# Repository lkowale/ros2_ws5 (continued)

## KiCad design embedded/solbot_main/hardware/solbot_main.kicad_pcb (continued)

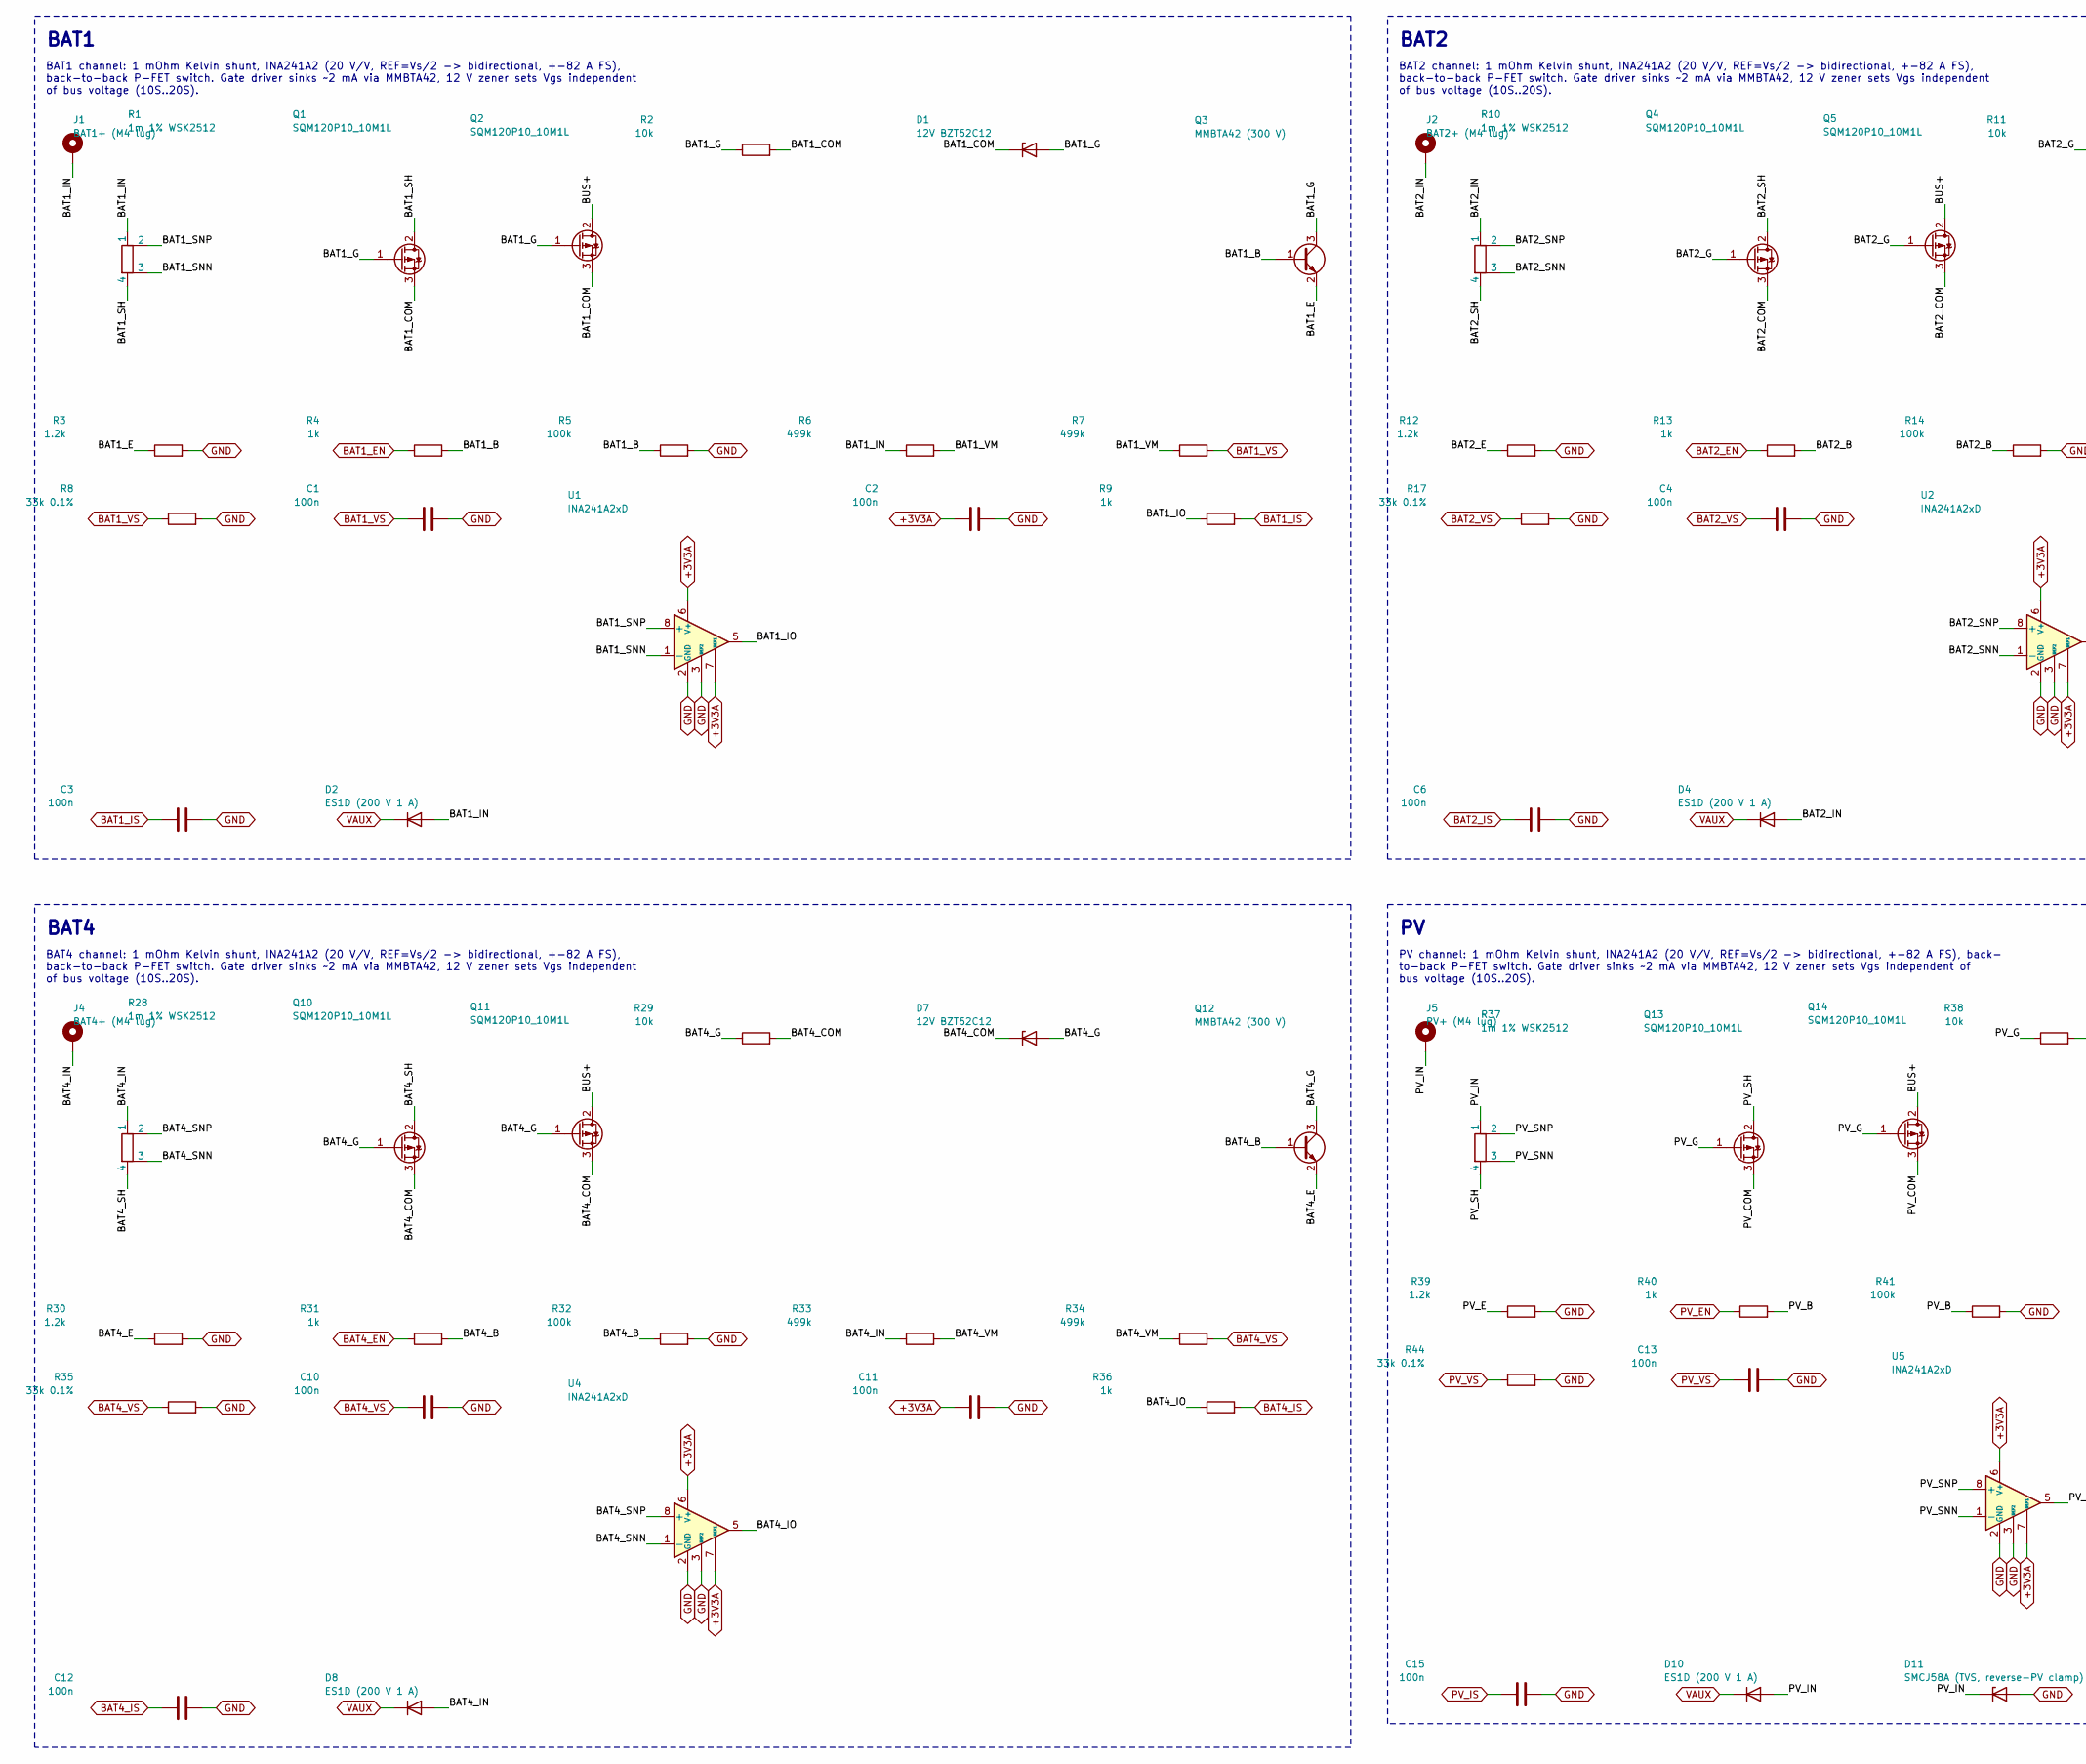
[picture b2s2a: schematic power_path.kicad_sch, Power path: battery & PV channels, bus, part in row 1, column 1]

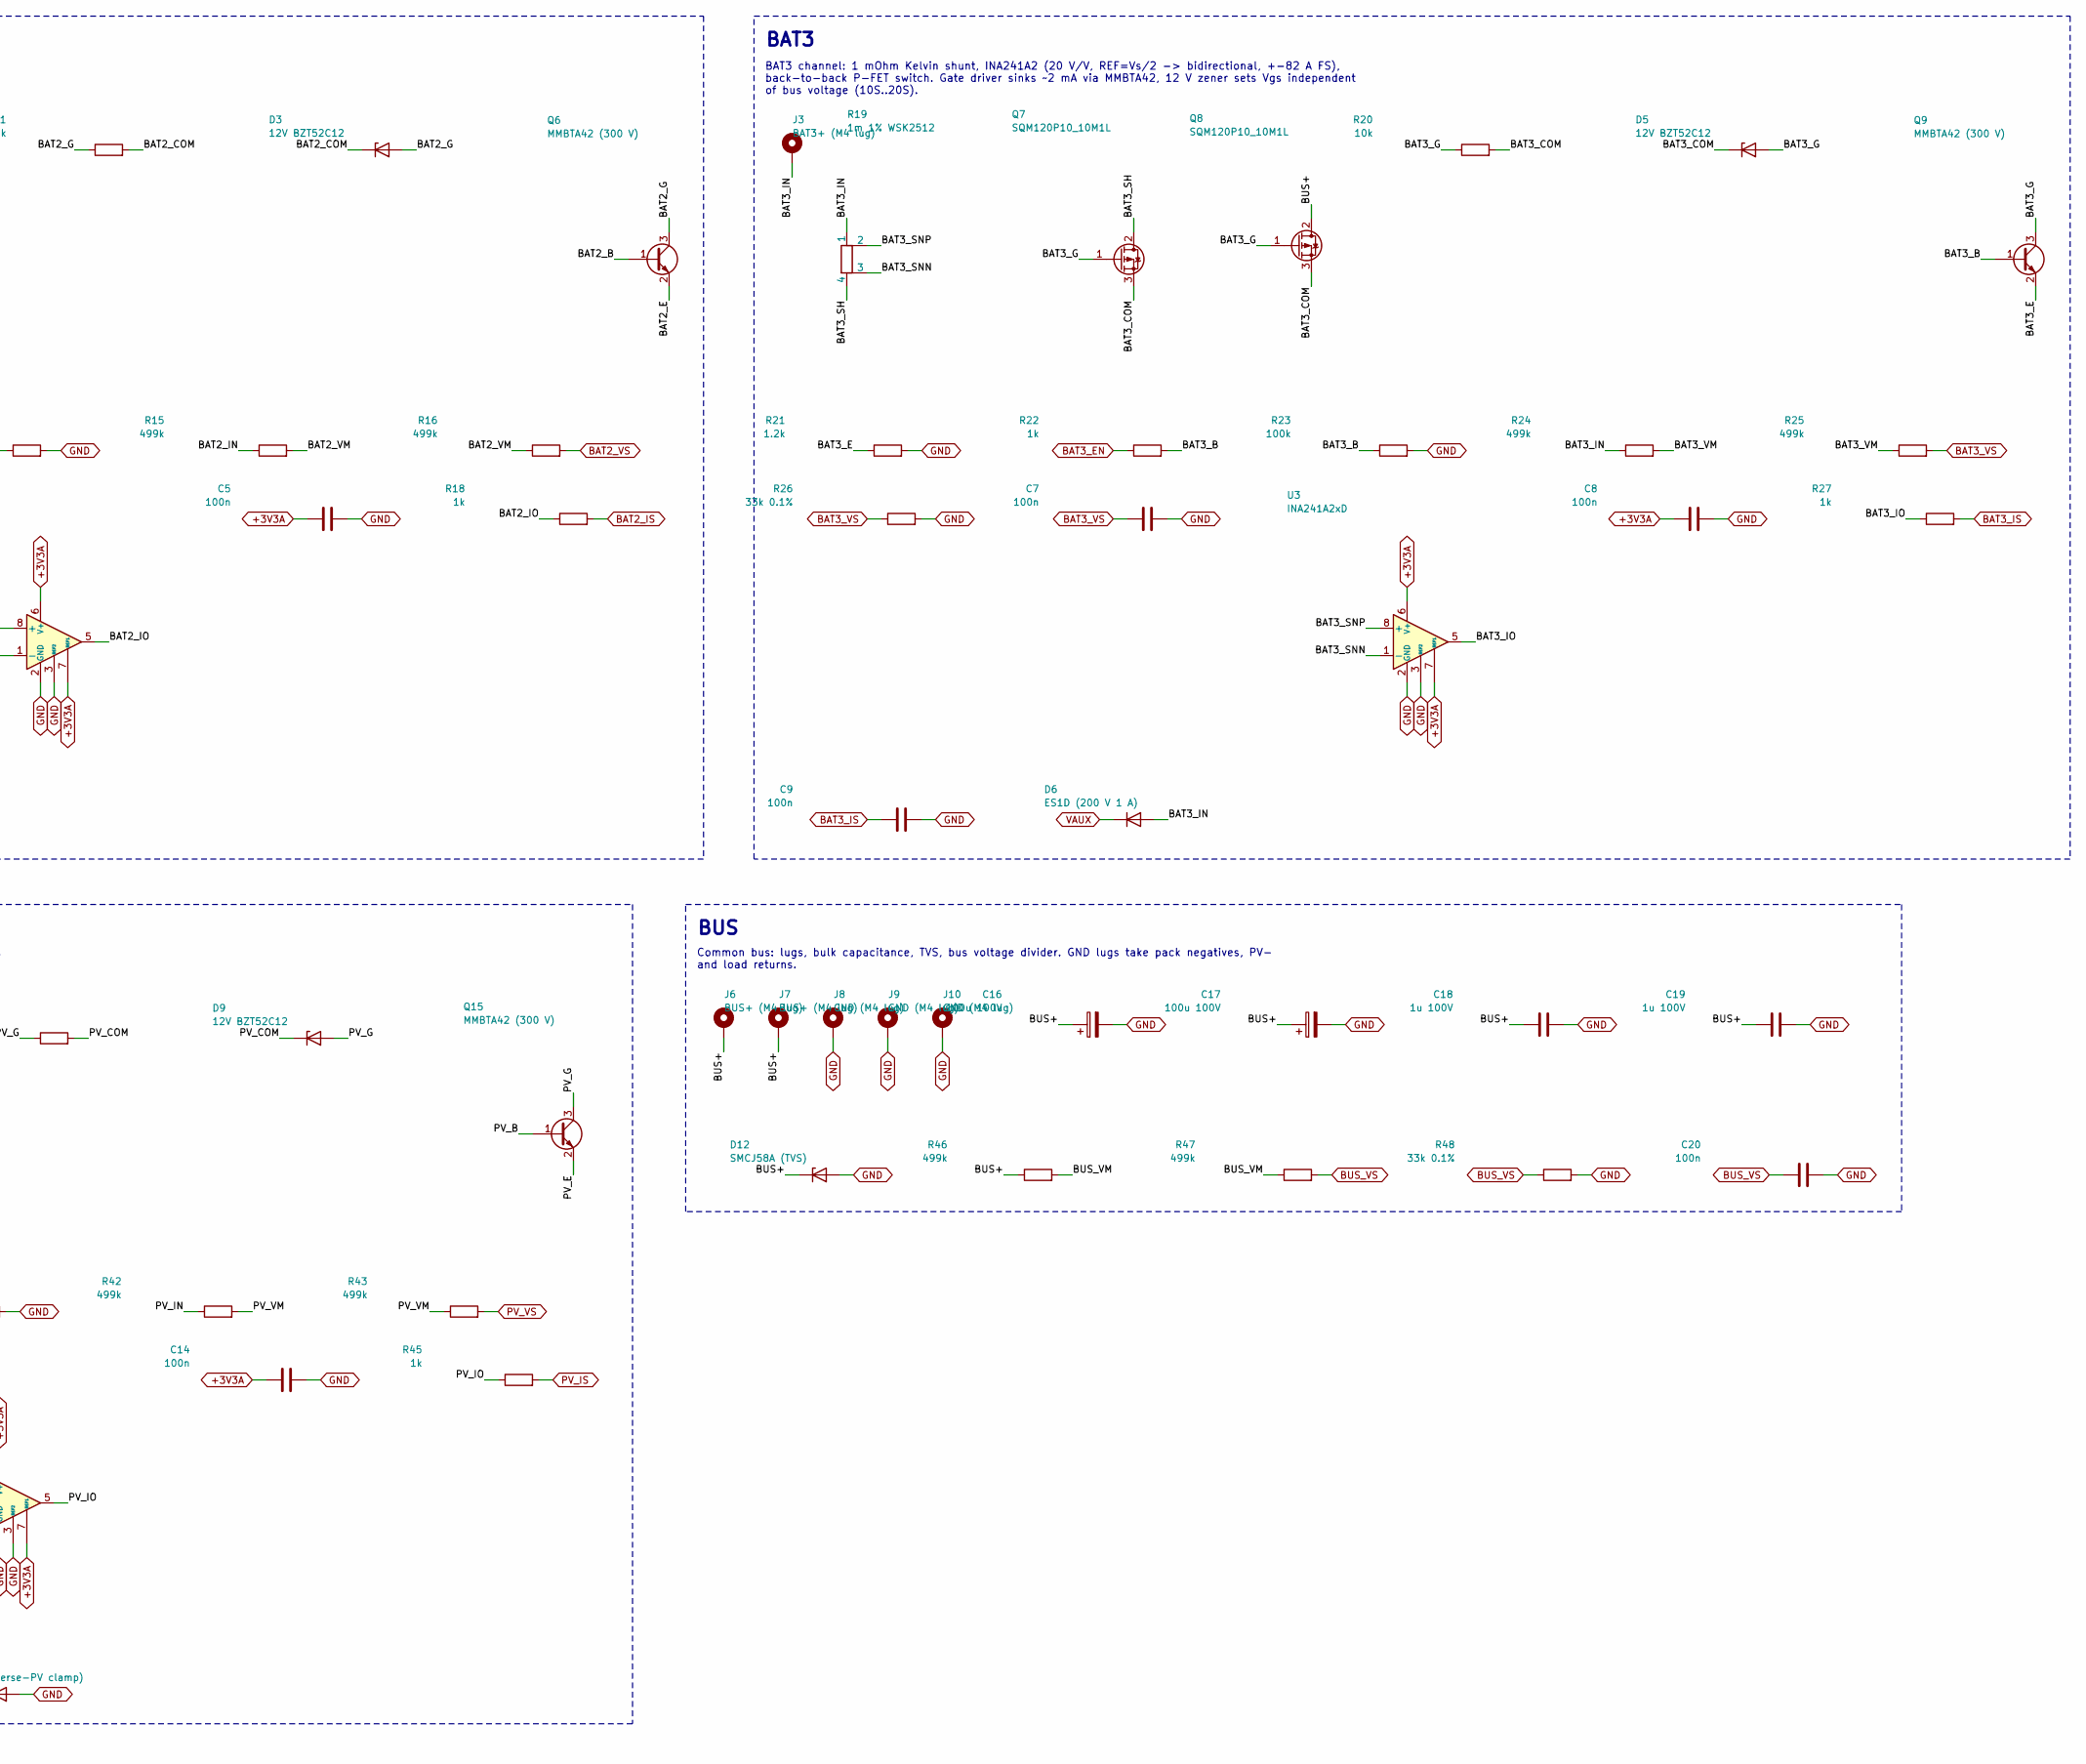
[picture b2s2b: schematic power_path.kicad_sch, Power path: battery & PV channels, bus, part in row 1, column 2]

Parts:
C1, C2, C3, C4, C5, C6, C7, C8, C9, C10, C11, C12, C13, C14, C15, C20: 100n; C_0603_1608Metric
C16, C17: 100u 100V; CP_Radial_D12.5mm_P5.00mm
C18, C19: 1u 100V; C_1210_3225Metric
D1, D3, D5, D7, D9: 12V BZT52C12; D_SOD-123
D2, D4, D6, D8, D10: ES1D (200 V 1 A); D_SMA
D11: SMCJ58A (TVS, reverse-PV clamp); D_SMC
D12: SMCJ58A (TVS); D_SMC
J1: BAT1+ (M4 lug); MountingHole_4.3mm_M4_Pad_Via
J2: BAT2+ (M4 lug); MountingHole_4.3mm_M4_Pad_Via
J3: BAT3+ (M4 lug); MountingHole_4.3mm_M4_Pad_Via
J4: BAT4+ (M4 lug); MountingHole_4.3mm_M4_Pad_Via
J5: PV+ (M4 lug); MountingHole_4.3mm_M4_Pad_Via
J6, J7: BUS+ (M4 lug); MountingHole_4.3mm_M4_Pad_Via
J8, J9, J10: GND (M4 lug); MountingHole_4.3mm_M4_Pad_Via
Q1, Q2, Q4, Q5, Q7, Q8, Q10, Q11, Q13, Q14: SQM120P10_10M1L; TO-263-2; MPN Vishay SQM120P10_10M1L (-100 V, 10 mOhm)
Q3, Q6, Q9, Q12, Q15: MMBTA42 (300 V); SOT-23
R1, R10, R19, R28, R37: 1m 1% WSK2512; R_Shunt_Vishay_WSK2512_6332Metric_T1.19mm; MPN Vishay WSK25121L000FEA
R2, R11, R20, R29, R38: 10k; R_0603_1608Metric
R3, R12, R21, R30, R39: 1.2k; R_0603_1608Metric
R4, R9, R13, R18, R22, R27, R31, R36, R40, R45: 1k; R_0603_1608Metric
R5, R14, R23, R32, R41: 100k; R_0603_1608Metric
R6, R7, R15, R16, R24, R25, R33, R34, R42, R43, R46, R47: 499k; R_1206_3216Metric
R8, R17, R26, R35, R44, R48: 33k 0.1%; R_0603_1608Metric
U1, U2, U3, U4, U5: INA241A2xD; SOIC-8_3.9x4.9mm_P1.27mm

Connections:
+3V3A: C2.1, C5.1, C8.1, C11.1, C14.1, U1.6 (V+), U1.7 (REF1), U2.6 (V+), U2.7 (REF1), U3.6 (V+), U3.7 (REF1), U4.6 (V+), U4.7 (REF1), U5.6 (V+), U5.7 (REF1); also elsewhere on the board
BAT1_B: Q3.1 (B), R4.2, R5.1
BAT1_COM: D1.1 (K), Q1.3 (S), Q2.3 (S), R2.2
BAT1_E: Q3.2 (E), R3.1
BAT1_EN: R4.1; also elsewhere on the board
BAT1_G: D1.2 (A), Q1.1 (G), Q2.1 (G), Q3.3 (C), R2.1
BAT1_IN: D2.2 (A), J1.1, R1.1, R6.1
BAT1_IO: R9.1, U1.5
BAT1_IS: C3.1, R9.2; also elsewhere on the board
BAT1_SH: Q1.2 (D), R1.4
BAT1_SNN: R1.3, U1.1 (-)
BAT1_SNP: R1.2, U1.8 (+)
BAT1_VM: R6.2, R7.1
BAT1_VS: C1.1, R7.2, R8.1; also elsewhere on the board
BAT2_B: Q6.1 (B), R13.2, R14.1
BAT2_COM: D3.1 (K), Q4.3 (S), Q5.3 (S), R11.2
BAT2_E: Q6.2 (E), R12.1
BAT2_EN: R13.1; also elsewhere on the board
BAT2_G: D3.2 (A), Q4.1 (G), Q5.1 (G), Q6.3 (C), R11.1
BAT2_IN: D4.2 (A), J2.1, R10.1, R15.1
BAT2_IO: R18.1, U2.5
BAT2_IS: C6.1, R18.2; also elsewhere on the board
BAT2_SH: Q4.2 (D), R10.4
BAT2_SNN: R10.3, U2.1 (-)
BAT2_SNP: R10.2, U2.8 (+)
BAT2_VM: R15.2, R16.1
BAT2_VS: C4.1, R16.2, R17.1; also elsewhere on the board
BAT3_B: Q9.1 (B), R22.2, R23.1
BAT3_COM: D5.1 (K), Q7.3 (S), Q8.3 (S), R20.2
BAT3_E: Q9.2 (E), R21.1
BAT3_EN: R22.1; also elsewhere on the board
BAT3_G: D5.2 (A), Q7.1 (G), Q8.1 (G), Q9.3 (C), R20.1
BAT3_IN: D6.2 (A), J3.1, R19.1, R24.1
BAT3_IO: R27.1, U3.5
BAT3_IS: C9.1, R27.2; also elsewhere on the board
BAT3_SH: Q7.2 (D), R19.4
BAT3_SNN: R19.3, U3.1 (-)
BAT3_SNP: R19.2, U3.8 (+)
BAT3_VM: R24.2, R25.1
BAT3_VS: C7.1, R25.2, R26.1; also elsewhere on the board
BAT4_B: Q12.1 (B), R31.2, R32.1
BAT4_COM: D7.1 (K), Q10.3 (S), Q11.3 (S), R29.2
BAT4_E: Q12.2 (E), R30.1
BAT4_EN: R31.1; also elsewhere on the board
BAT4_G: D7.2 (A), Q10.1 (G), Q11.1 (G), Q12.3 (C), R29.1
BAT4_IN: D8.2 (A), J4.1, R28.1, R33.1
BAT4_IO: R36.1, U4.5
BAT4_IS: C12.1, R36.2; also elsewhere on the board
BAT4_SH: Q10.2 (D), R28.4
BAT4_SNN: R28.3, U4.1 (-)
BAT4_SNP: R28.2, U4.8 (+)
BAT4_VM: R33.2, R34.1
BAT4_VS: C10.1, R34.2, R35.1; also elsewhere on the board
BUS+: C16.1, C17.1, C18.1, C19.1, D12.1 (K), J6.1, J7.1, Q2.2 (D), Q5.2 (D), Q8.2 (D), Q11.2 (D), Q14.2 (D), R46.1
BUS_VM: R46.2, R47.1
BUS_VS: C20.1, R47.2, R48.1; also elsewhere on the board
GND: C1.2, C2.2, C3.2, C4.2, C5.2, C6.2, C7.2, C8.2, C9.2, C10.2, C11.2, C12.2, C13.2, C14.2, C15.2, C16.2, C17.2, C18.2, C19.2, C20.2, D11.2 (A), D12.2 (A), J8.1, J9.1, J10.1, R3.2, R5.2, R8.2, R12.2, R14.2, R17.2, R21.2, R23.2, R26.2, R30.2, R32.2, R35.2, R39.2, R41.2, R44.2, R48.2, U1.2 (GND), U1.3 (REF2), U1.4 (GND), U2.2 (GND), U2.3 (REF2), U2.4 (GND), U3.2 (GND), U3.3 (REF2), U3.4 (GND), U4.2 (GND), U4.3 (REF2), U4.4 (GND), U5.2 (GND), U5.3 (REF2), U5.4 (GND); also elsewhere on the board
PV_B: Q15.1 (B), R40.2, R41.1
PV_COM: D9.1 (K), Q13.3 (S), Q14.3 (S), R38.2
PV_E: Q15.2 (E), R39.1
PV_EN: R40.1; also elsewhere on the board
PV_G: D9.2 (A), Q13.1 (G), Q14.1 (G), Q15.3 (C), R38.1
PV_IN: D10.2 (A), D11.1 (K), J5.1, R37.1, R42.1
PV_IO: R45.1, U5.5
PV_IS: C15.1, R45.2; also elsewhere on the board
PV_SH: Q13.2 (D), R37.4
PV_SNN: R37.3, U5.1 (-)
PV_SNP: R37.2, U5.8 (+)
PV_VM: R42.2, R43.1
PV_VS: C13.1, R43.2, R44.1; also elsewhere on the board
VAUX: D2.1 (K), D4.1 (K), D6.1 (K), D8.1 (K), D10.1 (K); also elsewhere on the board

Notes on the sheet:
BAT1
BAT1 channel: 1 mOhm Kelvin shunt, INA241A2 (20 V/V, REF=Vs/2 -> bidirectional, +-82 A FS), back-to-back P-FET switch. Gate driver sinks ~2 mA via MMBTA42, 12 V zener sets Vgs independent of bus voltage (10S..20S).
BAT2
BAT2 channel: 1 mOhm Kelvin shunt, INA241A2 (20 V/V, REF=Vs/2 -> bidirectional, +-82 A FS), back-to-back P-FET switch. Gate driver sinks ~2 mA via MMBTA42, 12 V zener sets Vgs independent of bus voltage (10S..20S).
BAT3
BAT3 channel: 1 mOhm Kelvin shunt, INA241A2 (20 V/V, REF=Vs/2 -> bidirectional, +-82 A FS), back-to-back P-FET switch. Gate driver sinks ~2 mA via MMBTA42, 12 V zener sets Vgs independent of bus voltage (10S..20S).
BAT4
BAT4 channel: 1 mOhm Kelvin shunt, INA241A2 (20 V/V, REF=Vs/2 -> bidirectional, +-82 A FS), back-to-back P-FET switch. Gate driver sinks ~2 mA via MMBTA42, 12 V zener sets Vgs independent of bus voltage (10S..20S).
PV channel: 1 mOhm Kelvin shunt, INA241A2 (20 V/V, REF=Vs/2 -> bidirectional, +-82 A FS), back- to-back P-FET switch. Gate driver sinks ~2 mA via MMBTA42, 12 V zener sets Vgs independent of bus voltage (10S..20S).
BUS
Common bus: lugs, bulk capacitance, TVS, bus voltage divider. GND lugs take pack negatives, PV- and load returns.

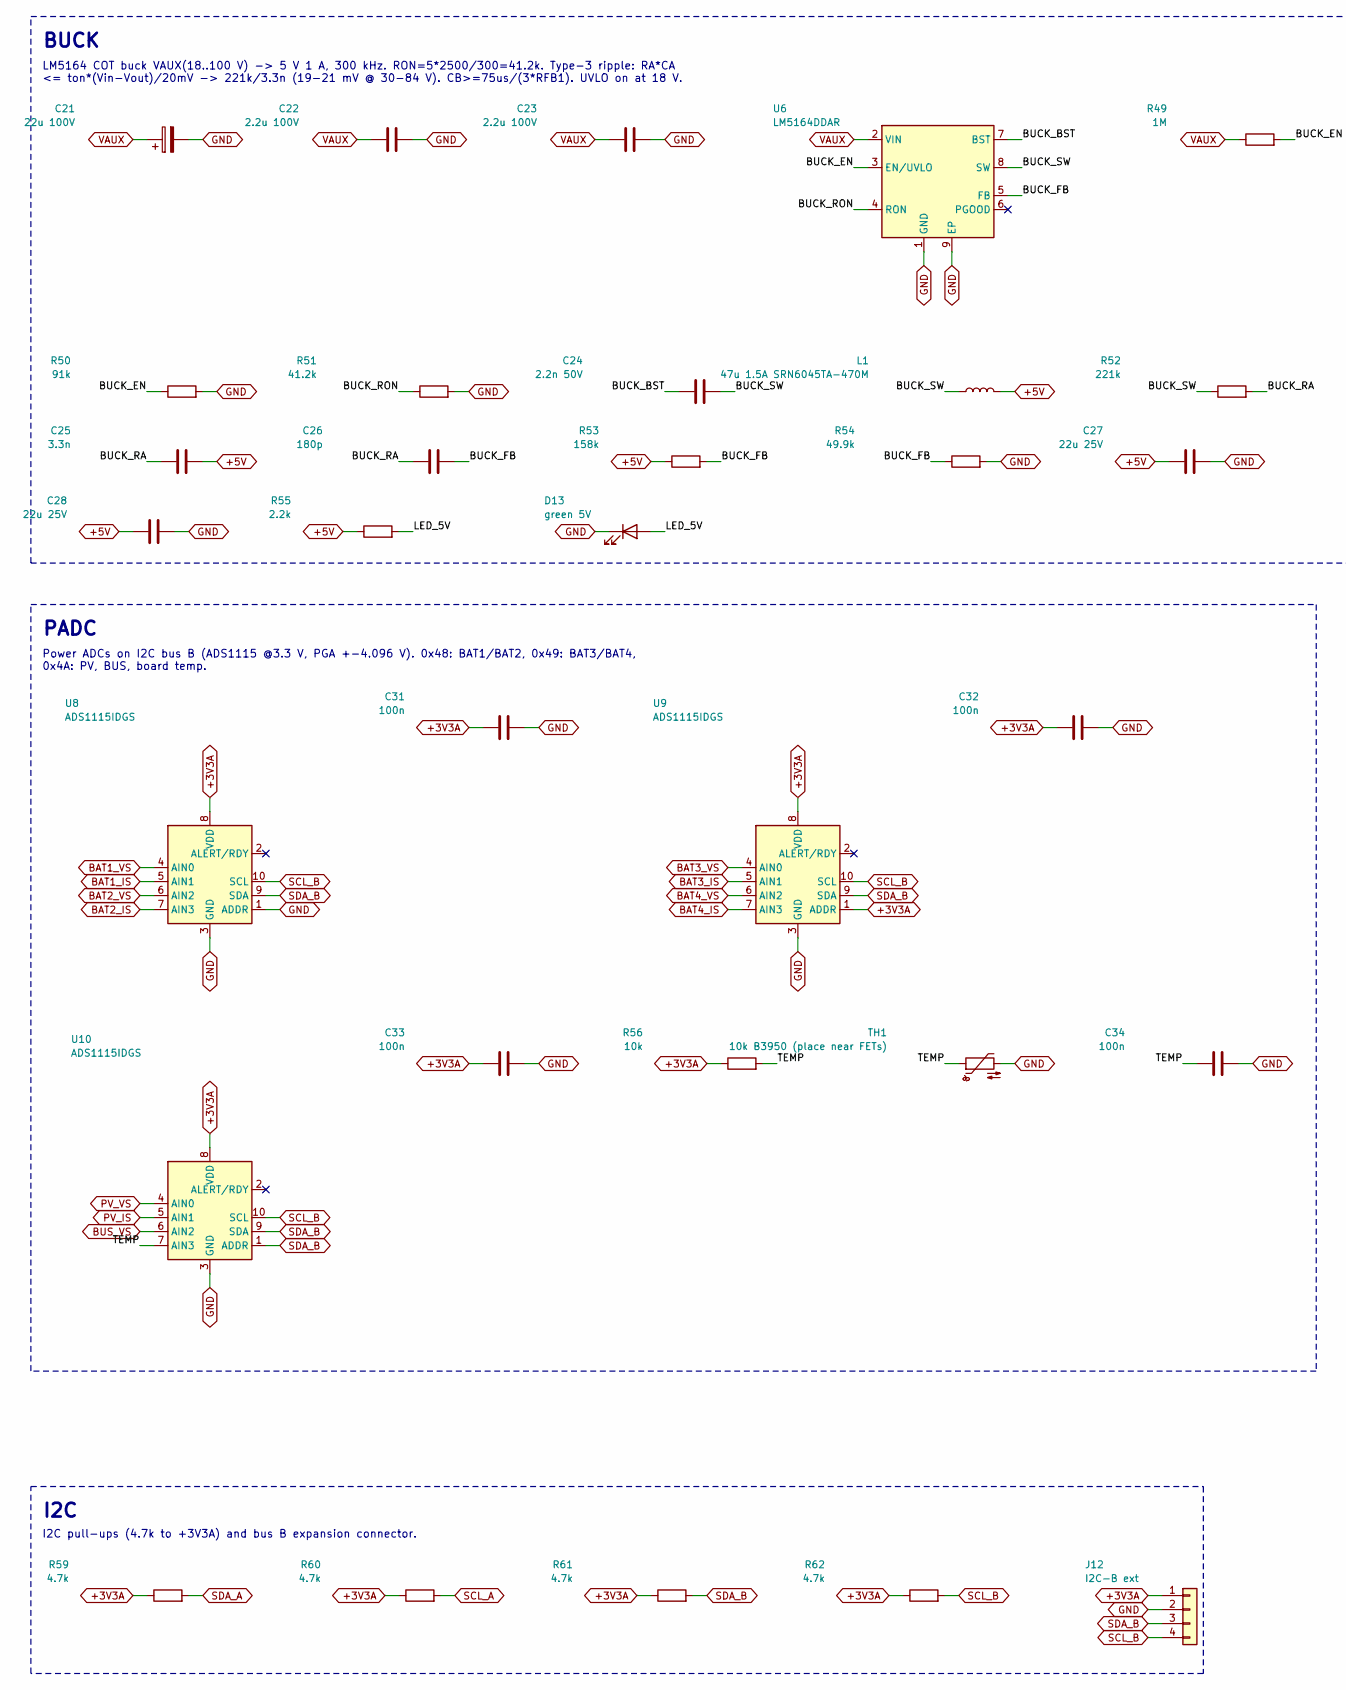
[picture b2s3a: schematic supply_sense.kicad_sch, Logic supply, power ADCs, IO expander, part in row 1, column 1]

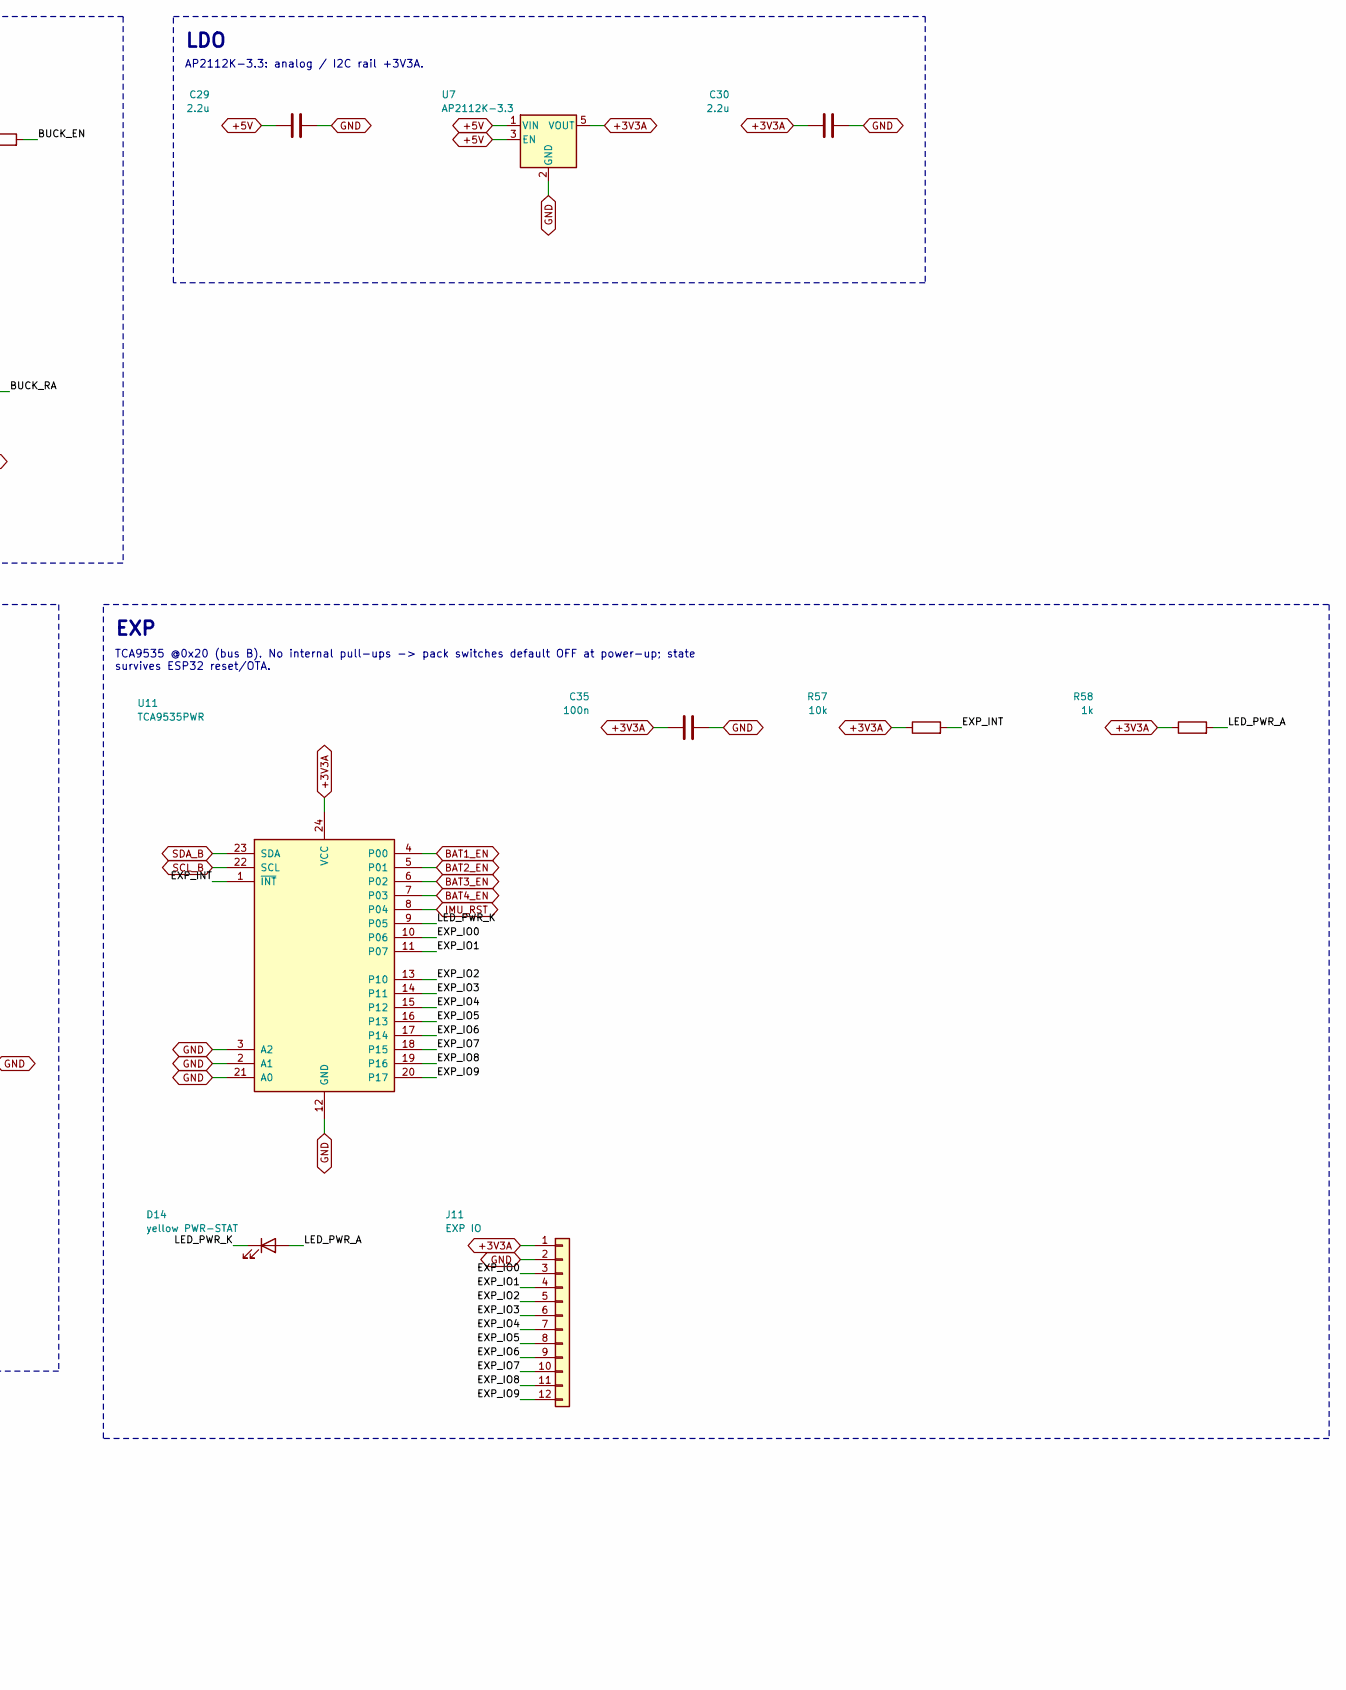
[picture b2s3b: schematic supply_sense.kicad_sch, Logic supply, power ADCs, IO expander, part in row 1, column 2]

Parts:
C21: 22u 100V; CP_Elec_8x10
C22, C23: 2.2u 100V; C_1210_3225Metric
C24: 2.2n 50V; C_0603_1608Metric
C25: 3.3n; C_0603_1608Metric
C26: 180p; C_0603_1608Metric
C27, C28: 22u 25V; C_1206_3216Metric
C29, C30: 2.2u; C_0805_2012Metric
C31, C32, C33, C34, C35: 100n; C_0603_1608Metric
D13: green 5V; LED_0603_1608Metric
D14: yellow PWR-STAT; LED_0603_1608Metric
J11: EXP IO; PinHeader_1x12_P2.54mm_Vertical
J12: I2C-B ext; JST_XH_B4B-XH-A_1x04_P2.50mm_Vertical
L1: 47u 1.5A SRN6045TA-470M; L_Bourns_SRN6045TA
R49: 1M; R_1206_3216Metric
R50: 91k; R_0603_1608Metric
R51: 41.2k; R_0603_1608Metric
R52: 221k; R_0603_1608Metric
R53: 158k; R_0603_1608Metric
R54: 49.9k; R_0603_1608Metric
R55: 2.2k; R_0603_1608Metric
R56, R57: 10k; R_0603_1608Metric
R58: 1k; R_0603_1608Metric
R59, R60, R61, R62: 4.7k; R_0603_1608Metric
TH1: 10k B3950 (place near FETs); R_0603_1608Metric
U6: LM5164DDAR; HSOP-8-1EP_3.9x4.9mm_P1.27mm_EP2.41x3.1mm_ThermalVias
U7: AP2112K-3.3; SOT-23-5
U8, U9, U10: ADS1115IDGS; TSSOP-10_3x3mm_P0.5mm
U11: TCA9535PWR; TSSOP-24_4.4x7.8mm_P0.65mm

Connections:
+3V3A: C30.1, C31.1, C32.1, C33.1, C35.1, J11.1, J12.1, R56.1, R57.1, R58.1, R59.1, R60.1, R61.1, R62.1, U7.5 (VOUT), U8.8 (VDD), U9.1 (ADDR), U9.8 (VDD), U10.8 (VDD), U11.24 (VCC); also elsewhere on the board
+5V: C25.2, C27.1, C28.1, C29.1, L1.2, R53.1, R55.1, U7.1 (VIN), U7.3 (EN); also elsewhere on the board
BAT1_EN: U11.4 (P00); also elsewhere on the board
BAT1_IS: U8.5 (AIN1); also elsewhere on the board
BAT1_VS: U8.4 (AIN0); also elsewhere on the board
BAT2_EN: U11.5 (P01); also elsewhere on the board
BAT2_IS: U8.7 (AIN3); also elsewhere on the board
BAT2_VS: U8.6 (AIN2); also elsewhere on the board
BAT3_EN: U11.6 (P02); also elsewhere on the board
BAT3_IS: U9.5 (AIN1); also elsewhere on the board
BAT3_VS: U9.4 (AIN0); also elsewhere on the board
BAT4_EN: U11.7 (P03); also elsewhere on the board
BAT4_IS: U9.7 (AIN3); also elsewhere on the board
BAT4_VS: U9.6 (AIN2); also elsewhere on the board
BUCK_BST: C24.1, U6.7 (BST)
BUCK_EN: R49.2, R50.1, U6.3 (EN/UVLO)
BUCK_FB: C26.2, R53.2, R54.1, U6.5 (FB)
BUCK_RA: C25.1, C26.1, R52.2
BUCK_RON: R51.1, U6.4 (RON)
BUCK_SW: C24.2, L1.1, R52.1, U6.8 (SW)
BUS_VS: U10.6 (AIN2); also elsewhere on the board
EXP_INT: R57.2, U11.1 (~INT)
EXP_IO0: J11.3, U11.10 (P06)
EXP_IO1: J11.4, U11.11 (P07)
EXP_IO2: J11.5, U11.13 (P10)
EXP_IO3: J11.6, U11.14 (P11)
EXP_IO4: J11.7, U11.15 (P12)
EXP_IO5: J11.8, U11.16 (P13)
EXP_IO6: J11.9, U11.17 (P14)
EXP_IO7: J11.10, U11.18 (P15)
EXP_IO8: J11.11, U11.19 (P16)
EXP_IO9: J11.12, U11.20 (P17)
GND: C21.2, C22.2, C23.2, C27.2, C28.2, C29.2, C30.2, C31.2, C32.2, C33.2, C34.2, C35.2, D13.1 (K), J11.2, J12.2, R50.2, R51.2, R54.2, TH1.2, U6.1 (GND), U6.9 (EP), U7.2 (GND), U8.1 (ADDR), U8.3 (GND), U9.3 (GND), U10.3 (GND), U11.2 (A1), U11.3 (A2), U11.12 (GND), U11.21 (A0); also elsewhere on the board
IMU_RST: U11.8 (P04); also elsewhere on the board
LED_5V: D13.2 (A), R55.2
LED_PWR_A: D14.2 (A), R58.2
LED_PWR_K: D14.1 (K), U11.9 (P05)
PV_IS: U10.5 (AIN1); also elsewhere on the board
PV_VS: U10.4 (AIN0); also elsewhere on the board
SCL_A: R60.2; also elsewhere on the board
SCL_B: J12.4, R62.2, U8.10 (SCL), U9.10 (SCL), U10.10 (SCL), U11.22 (SCL); also elsewhere on the board
SDA_A: R59.2; also elsewhere on the board
SDA_B: J12.3, R61.2, U8.9 (SDA), U9.9 (SDA), U10.1 (ADDR), U10.9 (SDA), U11.23 (SDA); also elsewhere on the board
TEMP: C34.1, R56.2, TH1.1, U10.7 (AIN3)
VAUX: C21.1, C22.1, C23.1, R49.1, U6.2 (VIN); also elsewhere on the board

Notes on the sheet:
BUCK
LM5164 COT buck VAUX(18..100 V) -> 5 V 1 A, 300 kHz. RON=5*2500/300=41.2k. Type-3 ripple: RA*CA <= ton*(Vin-Vout)/20mV -> 221k/3.3n (19-21 mV @ 30-84 V). CB>=75us/(3*RFB1). UVLO on at 18 V.
LDO
AP2112K-3.3: analog / I2C rail +3V3A.
PADC
Power ADCs on I2C bus B (ADS1115 @3.3 V, PGA +-4.096 V). 0x48: BAT1/BAT2, 0x49: BAT3/BAT4, 0x4A: PV, BUS, board temp.
EXP
TCA9535 @0x20 (bus B). No internal pull-ups -> pack switches default OFF at power-up; state survives ESP32 reset/OTA.
I2C
I2C pull-ups (4.7k to +3V3A) and bus B expansion connector.

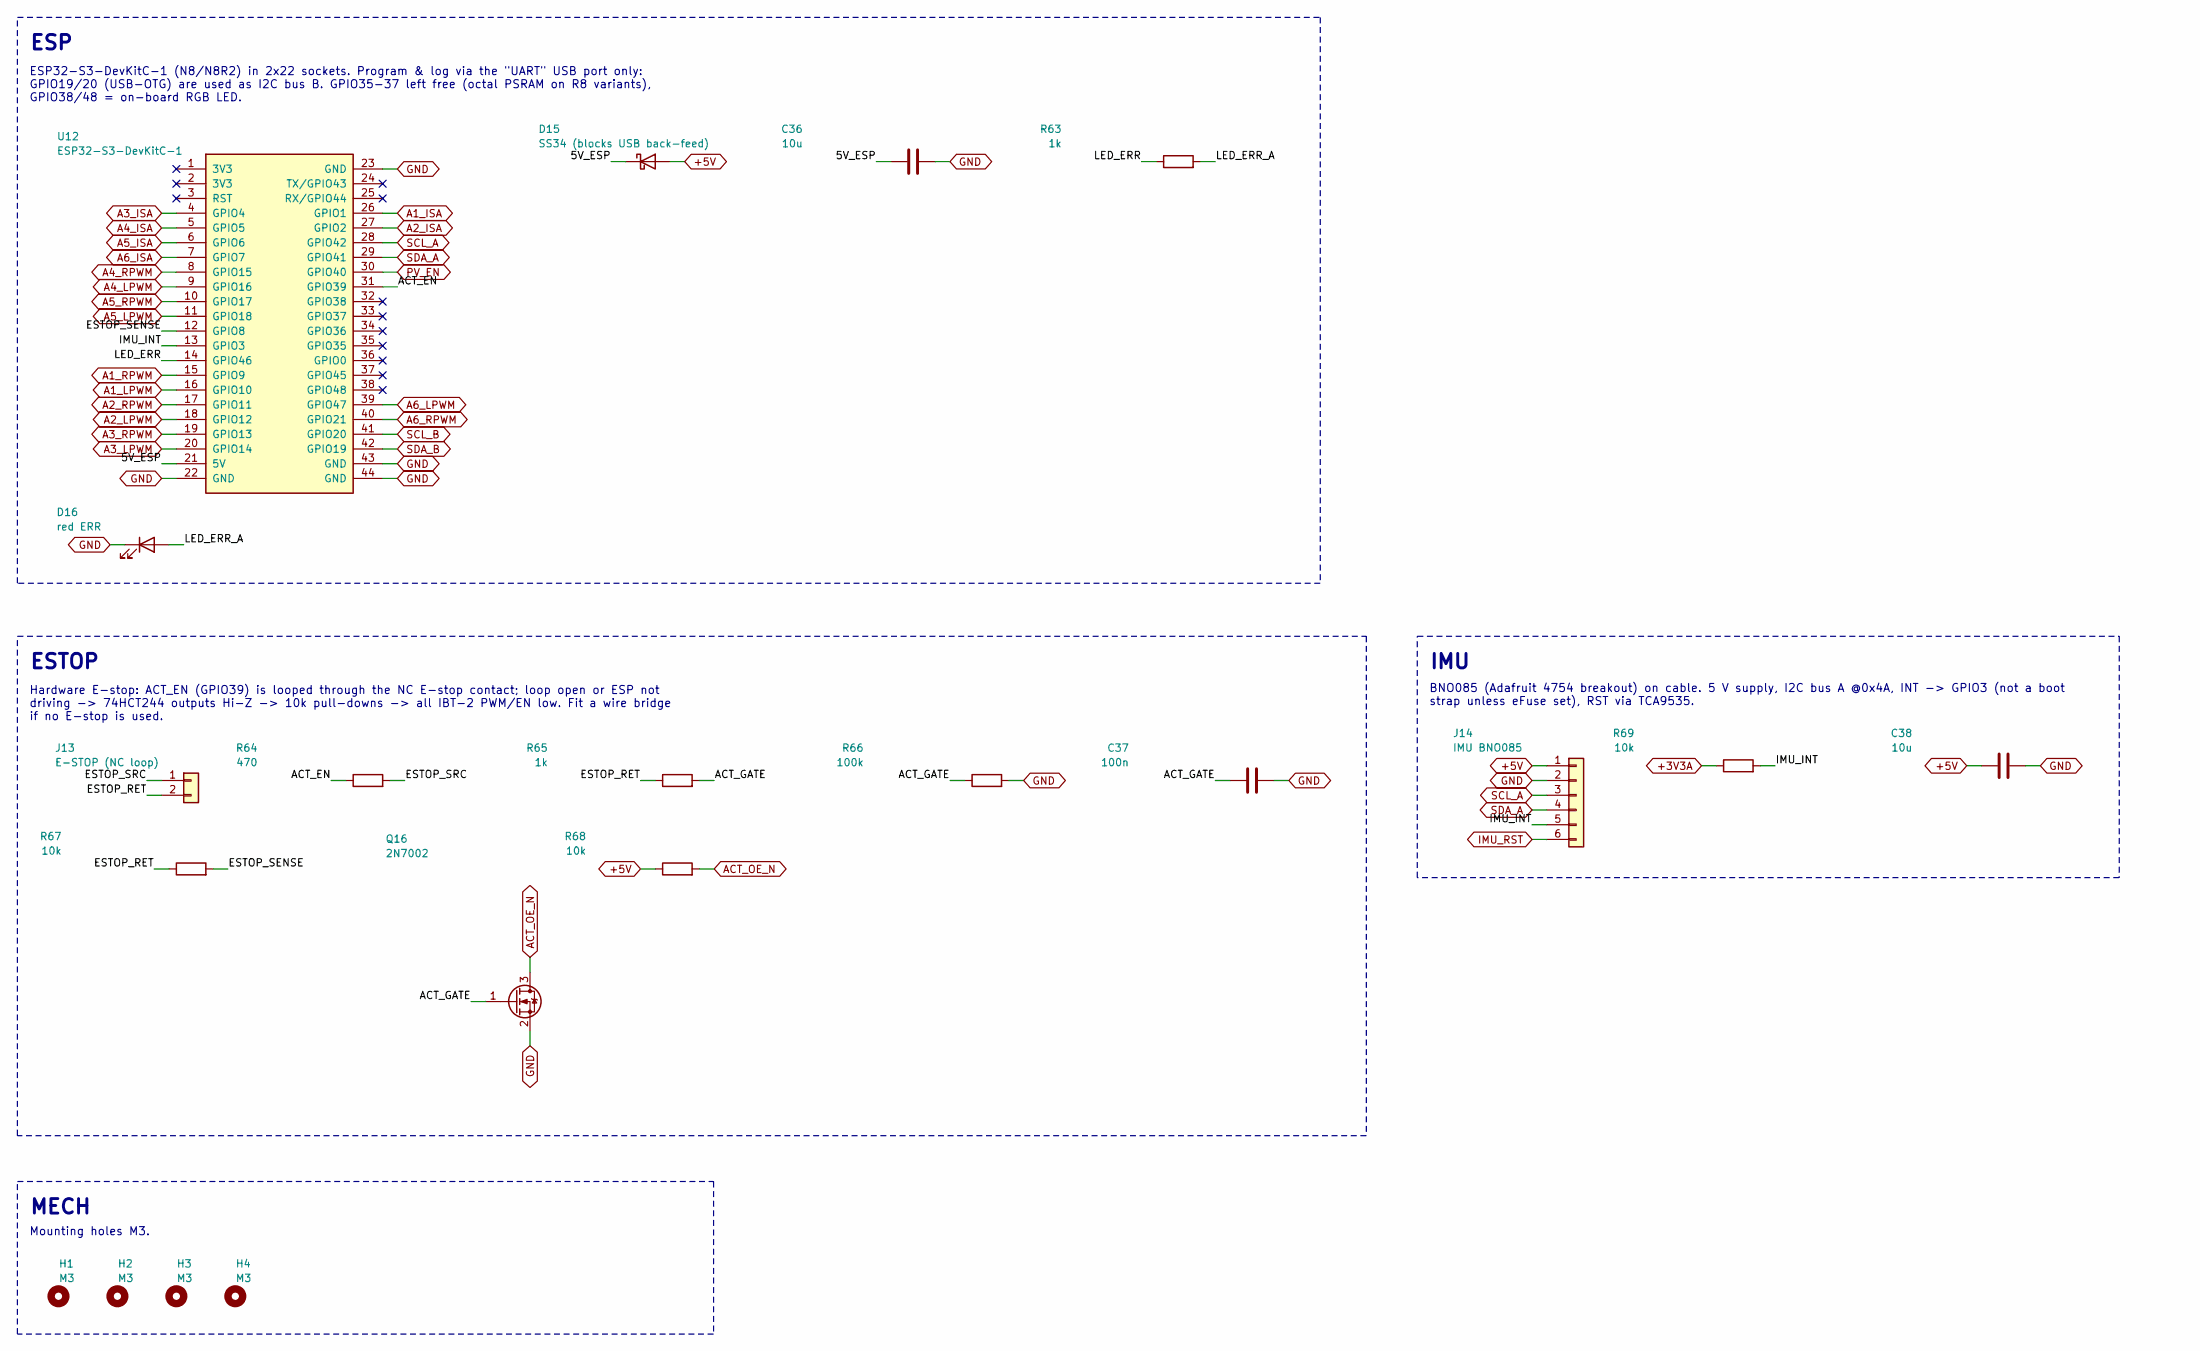
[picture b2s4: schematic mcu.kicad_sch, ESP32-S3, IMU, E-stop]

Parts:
C36, C38: 10u; C_0805_2012Metric
C37: 100n; C_0603_1608Metric
D15: SS34 (blocks USB back-feed); D_SMA
D16: red ERR; LED_0603_1608Metric
H1, H2, H3, H4: M3; MountingHole_3.2mm_M3
J13: E-STOP (NC loop); TerminalBlock_Phoenix_PT-1,5-2-3.5-H_1x02_P3.50mm_Horizontal
J14: IMU BNO085; JST_XH_B6B-XH-A_1x06_P2.50mm_Vertical
Q16: 2N7002; SOT-23
R63, R65: 1k; R_0603_1608Metric
R64: 470; R_0603_1608Metric
R66: 100k; R_0603_1608Metric
R67, R68, R69: 10k; R_0603_1608Metric
U12: ESP32-S3-DevKitC-1; ESP32-S3-DevKitC-1_Socket

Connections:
5V_ESP: C36.1, D15.1 (K), U12.21 (5V)
+3V3A: R69.1; also elsewhere on the board
+5V: C38.1, D15.2 (A), J14.1, R68.1; also elsewhere on the board
A1_ISA: U12.26 (GPIO1); also elsewhere on the board
A1_LPWM: U12.16 (GPIO10); also elsewhere on the board
A1_RPWM: U12.15 (GPIO9); also elsewhere on the board
A2_ISA: U12.27 (GPIO2); also elsewhere on the board
A2_LPWM: U12.18 (GPIO12); also elsewhere on the board
A2_RPWM: U12.17 (GPIO11); also elsewhere on the board
A3_ISA: U12.4 (GPIO4); also elsewhere on the board
A3_LPWM: U12.20 (GPIO14); also elsewhere on the board
A3_RPWM: U12.19 (GPIO13); also elsewhere on the board
A4_ISA: U12.5 (GPIO5); also elsewhere on the board
A4_LPWM: U12.9 (GPIO16); also elsewhere on the board
A4_RPWM: U12.8 (GPIO15); also elsewhere on the board
A5_ISA: U12.6 (GPIO6); also elsewhere on the board
A5_LPWM: U12.11 (GPIO18); also elsewhere on the board
A5_RPWM: U12.10 (GPIO17); also elsewhere on the board
A6_ISA: U12.7 (GPIO7); also elsewhere on the board
A6_LPWM: U12.39 (GPIO47); also elsewhere on the board
A6_RPWM: U12.40 (GPIO21); also elsewhere on the board
ACT_EN: R64.1, U12.31 (GPIO39)
ACT_GATE: C37.1, Q16.1 (G), R65.2, R66.1
ACT_OE_N: Q16.3 (D), R68.2; also elsewhere on the board
ESTOP_RET: J13.2, R65.1, R67.1
ESTOP_SENSE: R67.2, U12.12 (GPIO8)
ESTOP_SRC: J13.1, R64.2
GND: C36.2, C37.2, C38.2, D16.1 (K), J14.2, Q16.2 (S), R66.2, U12.22 (GND), U12.23 (GND), U12.43 (GND), U12.44 (GND); also elsewhere on the board
IMU_INT: J14.5, R69.2, U12.13 (GPIO3)
IMU_RST: J14.6; also elsewhere on the board
LED_ERR: R63.1, U12.14 (GPIO46)
LED_ERR_A: D16.2 (A), R63.2
PV_EN: U12.30 (GPIO40); also elsewhere on the board
SCL_A: J14.3, U12.28 (GPIO42); also elsewhere on the board
SCL_B: U12.41 (GPIO20); also elsewhere on the board
SDA_A: J14.4, U12.29 (GPIO41); also elsewhere on the board
SDA_B: U12.42 (GPIO19); also elsewhere on the board

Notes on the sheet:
ESP
ESP32-S3-DevKitC-1 (N8/N8R2) in 2x22 sockets. Program & log via the "UART" USB port only: GPIO19/20 (USB-OTG) are used as I2C bus B. GPIO35-37 left free (octal PSRAM on R8 variants), GPIO38/48 = on-board RGB LED.
ESTOP
Hardware E-stop: ACT_EN (GPIO39) is looped through the NC E-stop contact; loop open or ESP not driving -> 74HCT244 outputs Hi-Z -> 10k pull-downs -> all IBT-2 PWM/EN low. Fit a wire bridge if no E-stop is used.
IMU
BNO085 (Adafruit 4754 breakout) on cable. 5 V supply, I2C bus A @0x4A, INT -> GPIO3 (not a boot strap unless eFuse set), RST via TCA9535.
MECH
Mounting holes M3.
